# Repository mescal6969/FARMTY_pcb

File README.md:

Farmty – IoT Smart Farming System

Farmty is an IoT-based smart farming system designed to monitor and control farm parameters in real time.  
This repository contains the KiCad PCB design , schematics , and related files for the Farmty hardware.

##  Features
- ESP32-WROOM-32 microcontroller (with WiFi + Bluetooth)
- RS485 sensor support:
  - Soil moisture
  - pH sensor
  - EC (Electrical Conductivity)
  - Temperature
- BME280 (humidity, pressure, temperature sensor)
- Load cell integration (for smart weighing)
- OLED (SSD1306) display
- Stepper motor driver
- Relay control for automation
- PC817 optocoupler isolation
- USB-to-UART via CH340C
- Modular power supply and terminal blocks

---

##  Software
- **Firmware:** ESP-IDF / Arduino framework
- **Programming language:** Python (for data processing) + C++ (for microcontroller)
- **IoT Dashboard:** Cloud-ready, customizable with MQTT/HTTP

---

##  Hardware
- Designed in KiCad
- Includes hierarchical schematics for modularity
- PCB fabrication-ready

##  How to Use
1. Clone this repo:
   ```bash
   https://github.com/mescal6969/FARMTY_pcb
2. Open the project in KiCad.
3. Modify schematics/PCB as needed.
4. Generate Gerber files for manufacturing.
5.Flash ESP32 with firmware to connect to IoT dashboard.

## IoT Integration

Farmty uses the **ESP32 WiFi module** to connect to the cloud.  
It can be integrated with:  
- **Blynk**  
- **ThingsBoard**  
- **Node-RED**  
- **MQTT brokers** (Mosquitto, HiveMQ)  

## License

This project is open-source under the **MIT License**.  
Feel free to use, modify, and share with attribution.

 Author
Allan Ng’ang’a Gacheru
BSc Mechatronics Engineering
Dedan Kimathi University of Technology

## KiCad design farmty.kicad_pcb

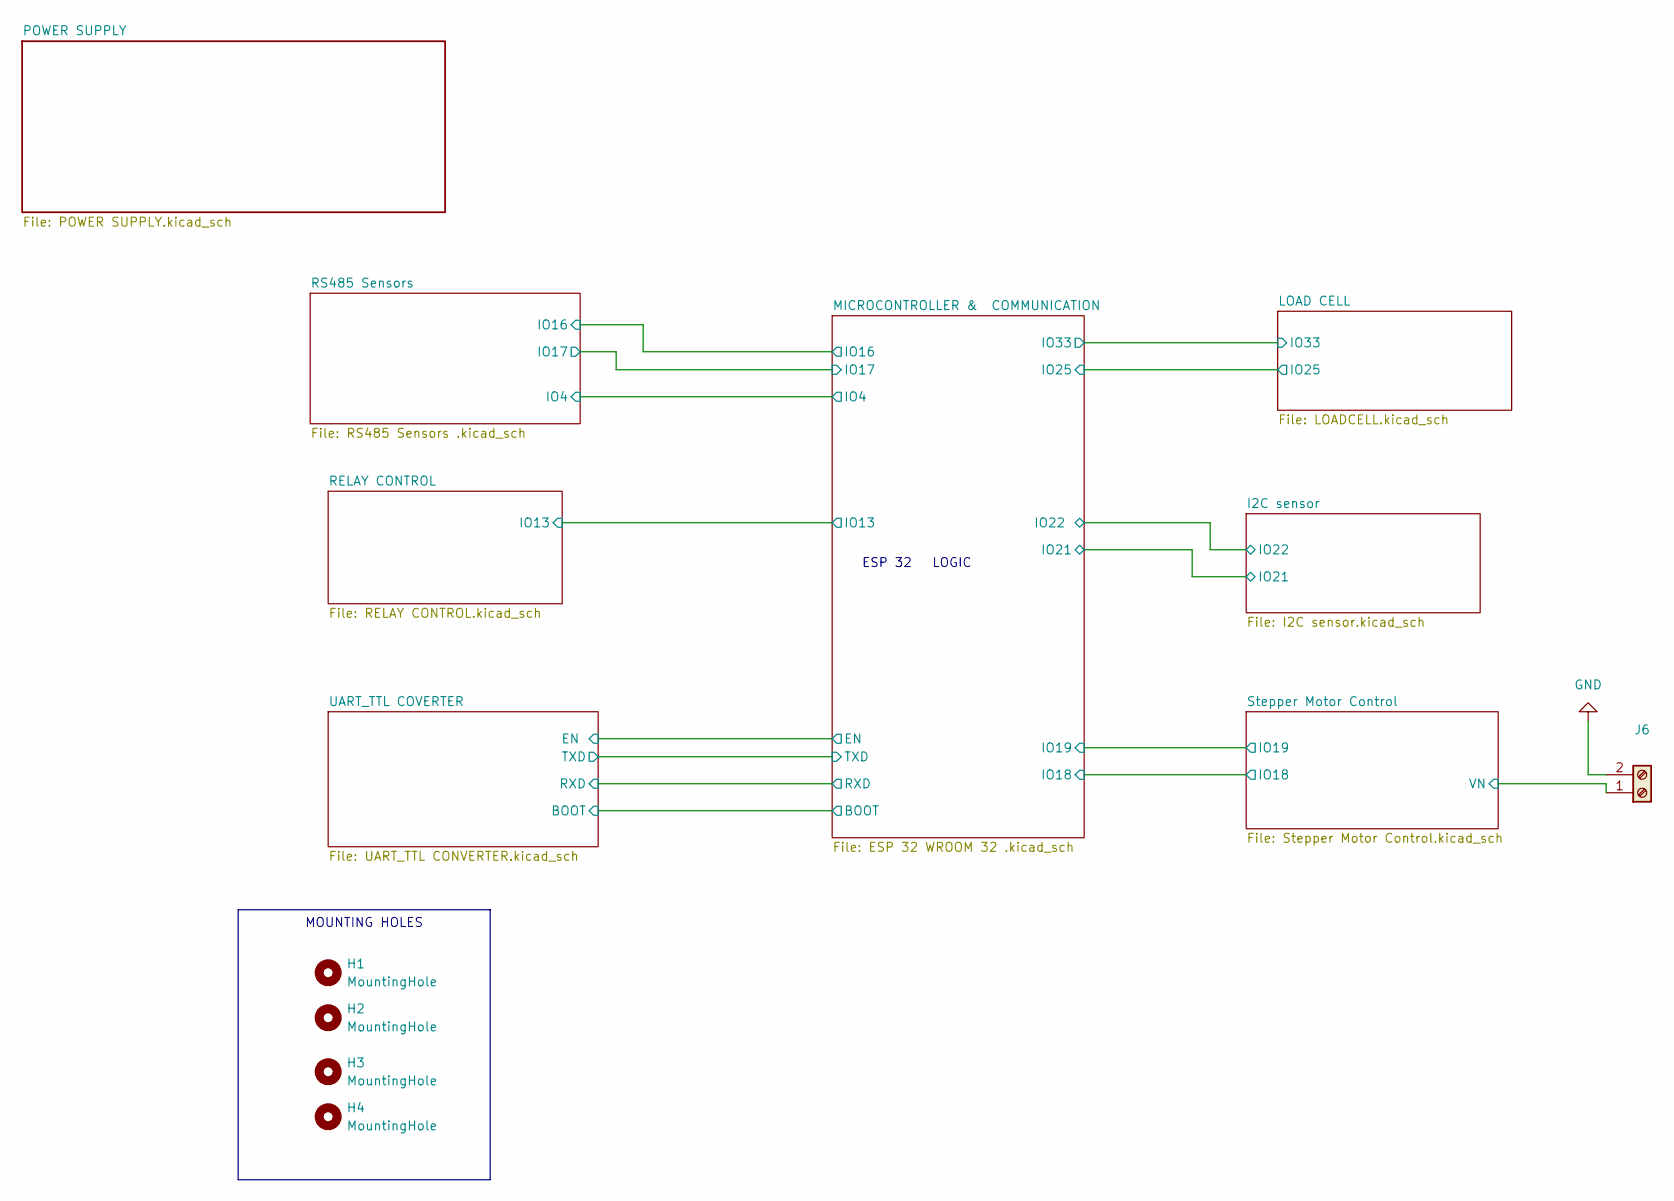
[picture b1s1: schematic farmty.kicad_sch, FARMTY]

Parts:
H1, H2, H3, H4: MountingHole; MountingHole_3.2mm_M3
J6: TerminalBlock_4Ucon_1x02_P3.50mm_Vertical

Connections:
/Stepper Motor Control/VN: J6.1; also elsewhere on the board
GND: J6.2; also elsewhere on the board

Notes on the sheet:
MOUNTING HOLES
ESP 32 LOGIC

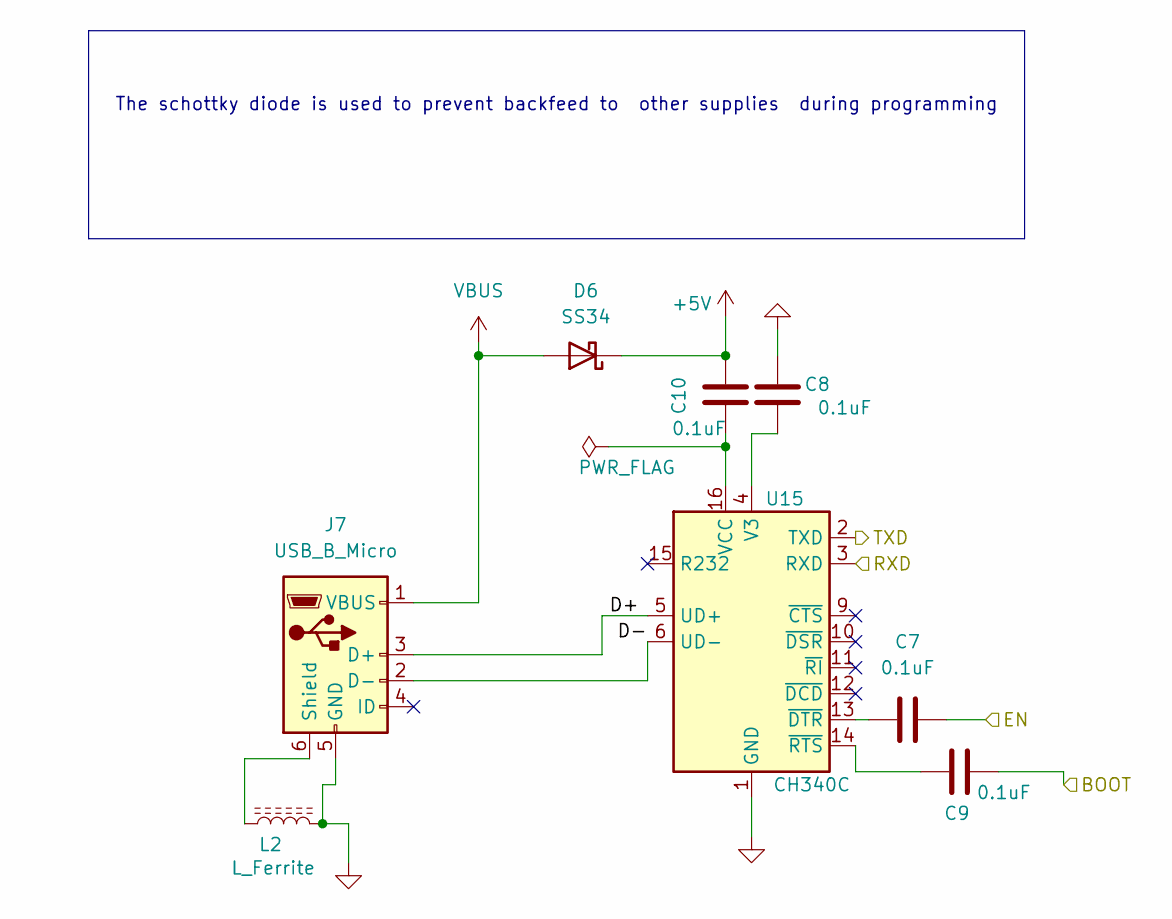
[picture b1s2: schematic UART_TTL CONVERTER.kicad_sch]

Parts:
C7, C8, C9, C10: 0.1uF; C_1808_4520Metric
D6: SS34; D_SMA
J7: USB_B_Micro; USB_Micro-B_Molex-105017-0001
L2: L_Ferrite; L_1806_4516Metric
U15: CH340C; SOIC-16_3.9x9.9mm_P1.27mm

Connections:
+5V: C10.1, D6.1 (K); also elsewhere on the board
/MICROCONTROLLER & COMMUNICATION/BOOT: C9.2; also elsewhere on the board
/MICROCONTROLLER & COMMUNICATION/EN: C7.2; also elsewhere on the board
/MICROCONTROLLER & COMMUNICATION/RXD: U15.3 (RXD); also elsewhere on the board
/MICROCONTROLLER & COMMUNICATION/TXD: U15.2 (TXD); also elsewhere on the board
GND: C8.1, J7.5 (GND), L2.2, U15.1 (GND); also elsewhere on the board
unnamed: J7.3 (D+), U15.5 (UD+)
unnamed: J7.2 (D-), U15.6 (UD-)
unnamed: J7.6 (Shield), L2.1
unnamed: C8.2, U15.4 (V3)
unnamed: C10.2, U15.16 (VCC)
unnamed: C7.1, U15.13 (~DTR)
unnamed: C9.1, U15.14 (~RTS)
VBUS: D6.2 (A), J7.1 (VBUS)

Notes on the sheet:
The schottky diode is used to prevent backfeed to other supplies during programming

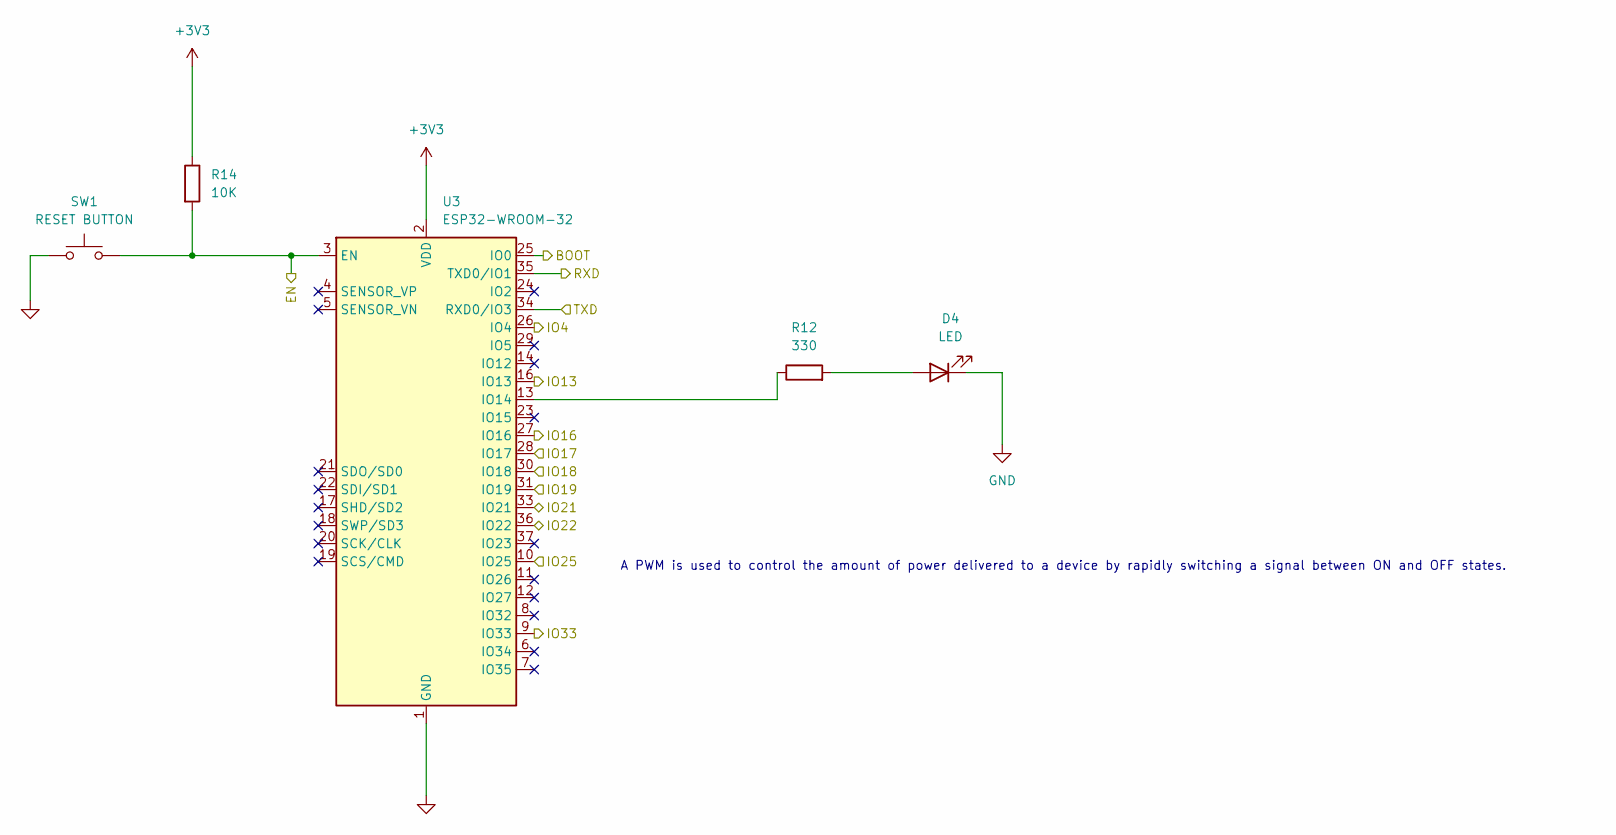
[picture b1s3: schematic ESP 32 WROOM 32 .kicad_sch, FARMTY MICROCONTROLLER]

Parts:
D4: LED; LED_2010_5025Metric
R12: 330; R_0603_1608Metric
R14: 10K; R_0603_1608Metric
SW1: RESET BUTTON; SW_DIP_SPSTx01_Slide_9.78x4.72mm_W7.62mm_P2.54mm
U3: ESP32-WROOM-32

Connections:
+3V3: R14.1, U3.2 (VDD); also elsewhere on the board
/I2C sensor/IO21: U3.33 (IO21); also elsewhere on the board
/I2C sensor/IO22: U3.36 (IO22); also elsewhere on the board
/LOAD CELL/IO25: U3.10 (IO25); also elsewhere on the board
/LOAD CELL/IO33: U3.9 (IO33); also elsewhere on the board
/MICROCONTROLLER & COMMUNICATION/BOOT: U3.25 (IO0); also elsewhere on the board
/MICROCONTROLLER & COMMUNICATION/EN: R14.2, SW1.2, U3.3 (EN); also elsewhere on the board
/MICROCONTROLLER & COMMUNICATION/IO4: U3.26 (IO4); also elsewhere on the board
/MICROCONTROLLER & COMMUNICATION/IO13: U3.16 (IO13); also elsewhere on the board
/MICROCONTROLLER & COMMUNICATION/IO16: U3.27 (IO16); also elsewhere on the board
/MICROCONTROLLER & COMMUNICATION/IO17: U3.28 (IO17); also elsewhere on the board
/MICROCONTROLLER & COMMUNICATION/IO18: U3.30 (IO18); also elsewhere on the board
/MICROCONTROLLER & COMMUNICATION/IO19: U3.31 (IO19); also elsewhere on the board
/MICROCONTROLLER & COMMUNICATION/RXD: U3.35 (TXD0/IO1); also elsewhere on the board
/MICROCONTROLLER & COMMUNICATION/TXD: U3.34 (RXD0/IO3); also elsewhere on the board
GND: D4.1 (K), SW1.1, U3.1 (GND), U3.15 (GND), U3.38 (GND), U3.39 (GND); also elsewhere on the board
unnamed: D4.2 (A), R12.2
unnamed: R12.1, U3.13 (IO14)

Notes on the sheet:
A PWM is used to control the amount of power delivered to a device by rapidly switching a signal between ON and OFF states.

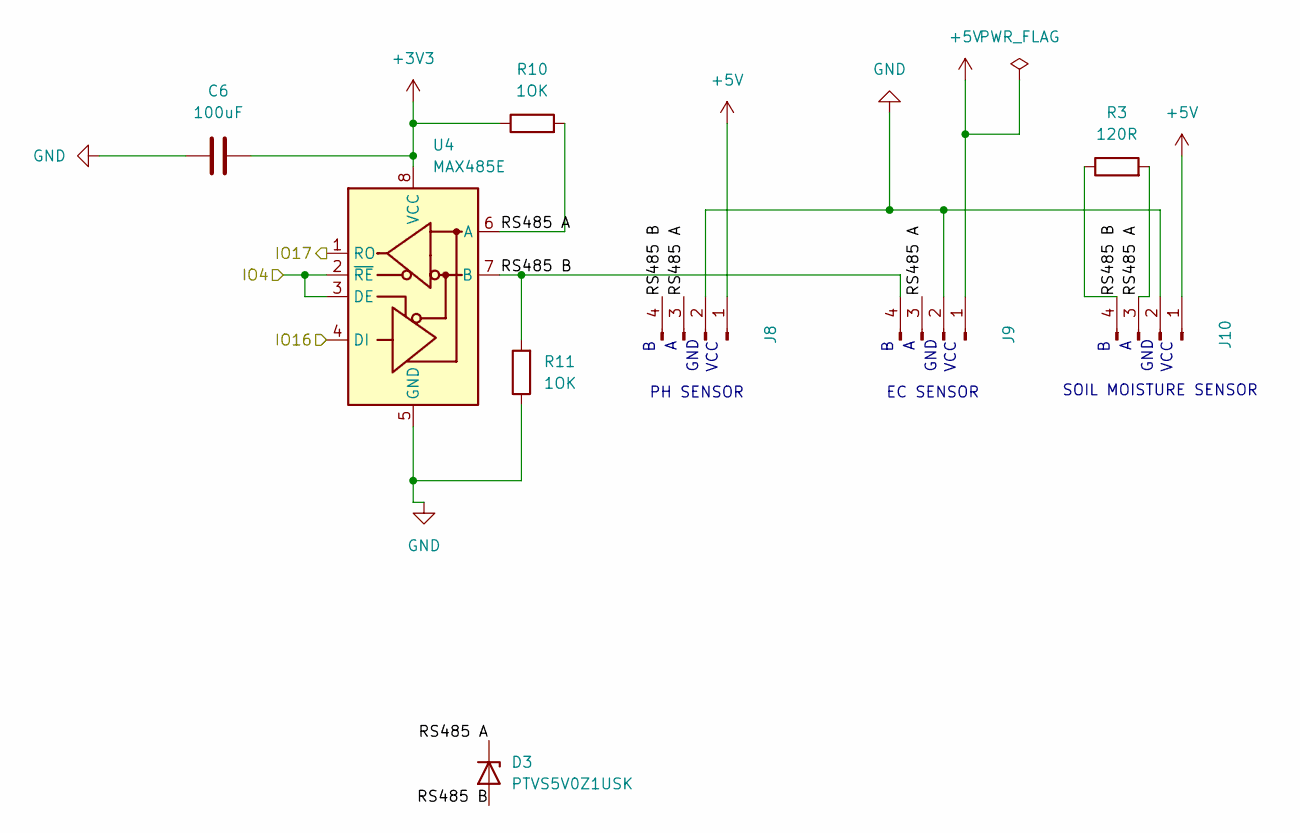
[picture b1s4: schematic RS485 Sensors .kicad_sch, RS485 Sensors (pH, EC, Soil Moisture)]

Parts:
C6: 100uF; C_2220_5750Metric
D3: PTVS5V0Z1USK; Nexperia_DSN1608-2_1.6x0.8mm
J8, J9, J10: Conn_01x04_Pin; PinHeader_1x04_P2.54mm_Vertical
R3: 120R; R_0603_1608Metric
R10, R11: 1OK; R_0603_1608Metric
U4: MAX485E; SOIC-8_3.9x4.9mm_P1.27mm

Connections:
+3V3: C6.2, R10.1, U4.8 (VCC); also elsewhere on the board
+5V: J8.1, J9.1, J10.1; also elsewhere on the board
/MICROCONTROLLER & COMMUNICATION/IO4: U4.2 (~RE), U4.3 (DE); also elsewhere on the board
/MICROCONTROLLER & COMMUNICATION/IO16: U4.4 (DI); also elsewhere on the board
/MICROCONTROLLER & COMMUNICATION/IO17: U4.1 (RO); also elsewhere on the board
/RS485 Sensors/RS485 A: D3.1 (K), J8.3, J9.3, J10.3, R3.2, R10.2, U4.6 (A)
/RS485 Sensors/RS485 B: D3.2 (A), J8.4, J9.4, J10.4, R3.1, R11.2, U4.7 (B)
GND: C6.1, J8.2, J9.2, J10.2, R11.1, U4.5 (GND); also elsewhere on the board

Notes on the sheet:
VCC
EC SENSOR
GND
PH SENSOR
SOIL MOISTURE SENSOR

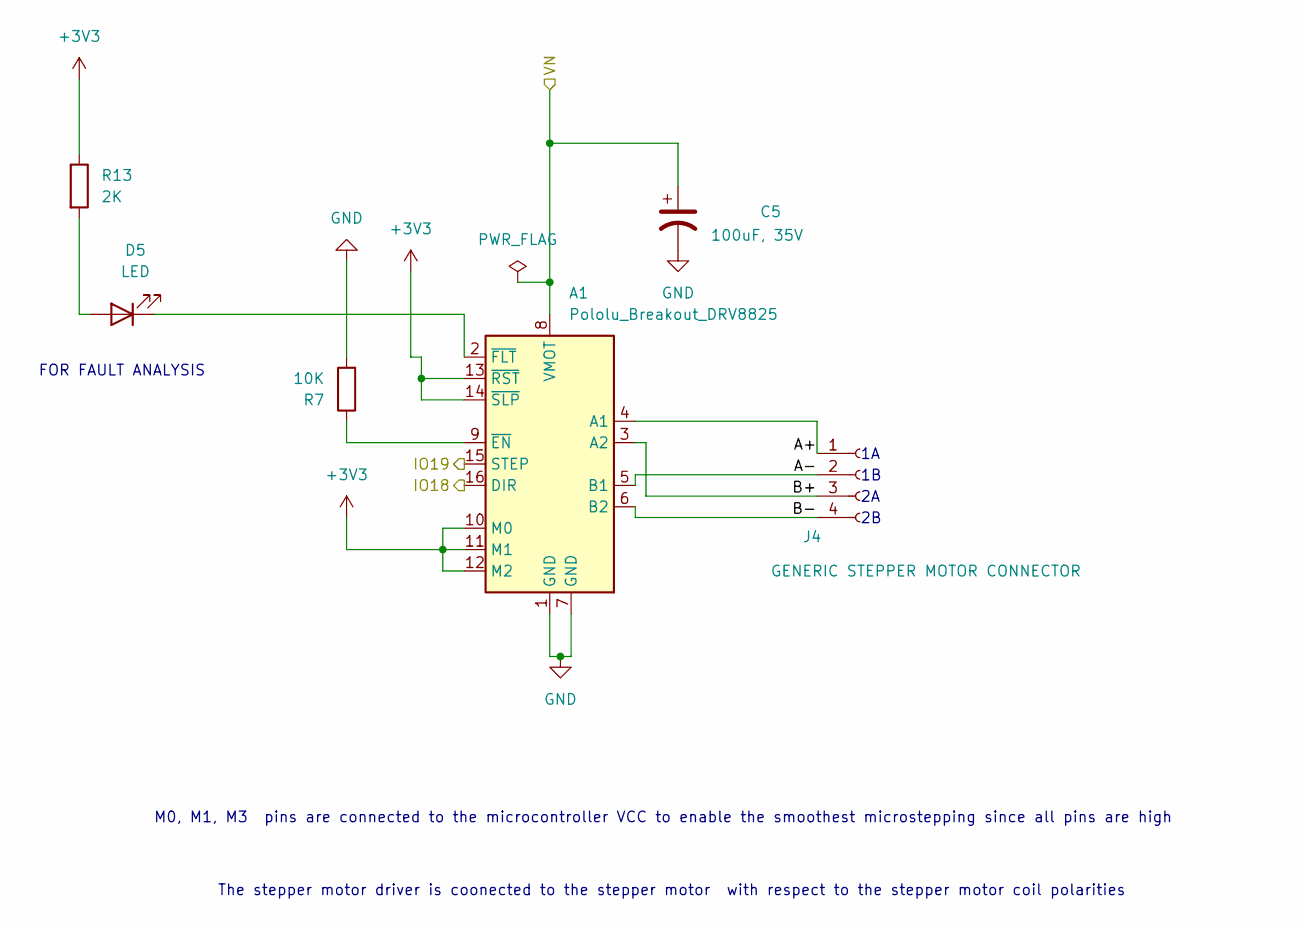
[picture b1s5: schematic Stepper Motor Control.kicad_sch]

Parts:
A1: Pololu_Breakout_DRV8825; Pololu_Breakout-16_15.2x20.3mm
C5: 100uF, 35V; C_2220_5750Metric
D5: LED; LED_D3.0mm
J4: GENERIC STEPPER MOTOR CONNECTOR; PinHeader_1x04_P2.54mm_Vertical
R7: 10K; R_0603_1608Metric
R13: 2K; R_0603_1608Metric

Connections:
+3V3: A1.10 (M0), A1.11 (M1), A1.12 (M2), A1.13 (~RST), A1.14 (~SLP), R13.1; also elsewhere on the board
/MICROCONTROLLER & COMMUNICATION/IO18: A1.16 (DIR); also elsewhere on the board
/MICROCONTROLLER & COMMUNICATION/IO19: A1.15 (STEP); also elsewhere on the board
/Stepper Motor Control/A+: A1.4 (A1), J4.1
/Stepper Motor Control/A-: A1.5 (B1), J4.2
/Stepper Motor Control/B+: A1.3 (A2), J4.3
/Stepper Motor Control/B-: A1.6 (B2), J4.4
/Stepper Motor Control/VN: A1.8 (VMOT), C5.1; also elsewhere on the board
GND: A1.1 (GND), A1.7 (GND), C5.2, R7.2; also elsewhere on the board
unnamed: A1.9 (~EN), R7.1
unnamed: A1.2 (~FLT), D5.1 (K)
unnamed: D5.2 (A), R13.2

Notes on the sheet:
M0, M1, M3 pins are connected to the microcontroller VCC to enable the smoothest microstepping since all pins are high
The stepper motor driver is coonected to the stepper motor with respect to the stepper motor coil polarities
FOR FAULT ANALYSIS

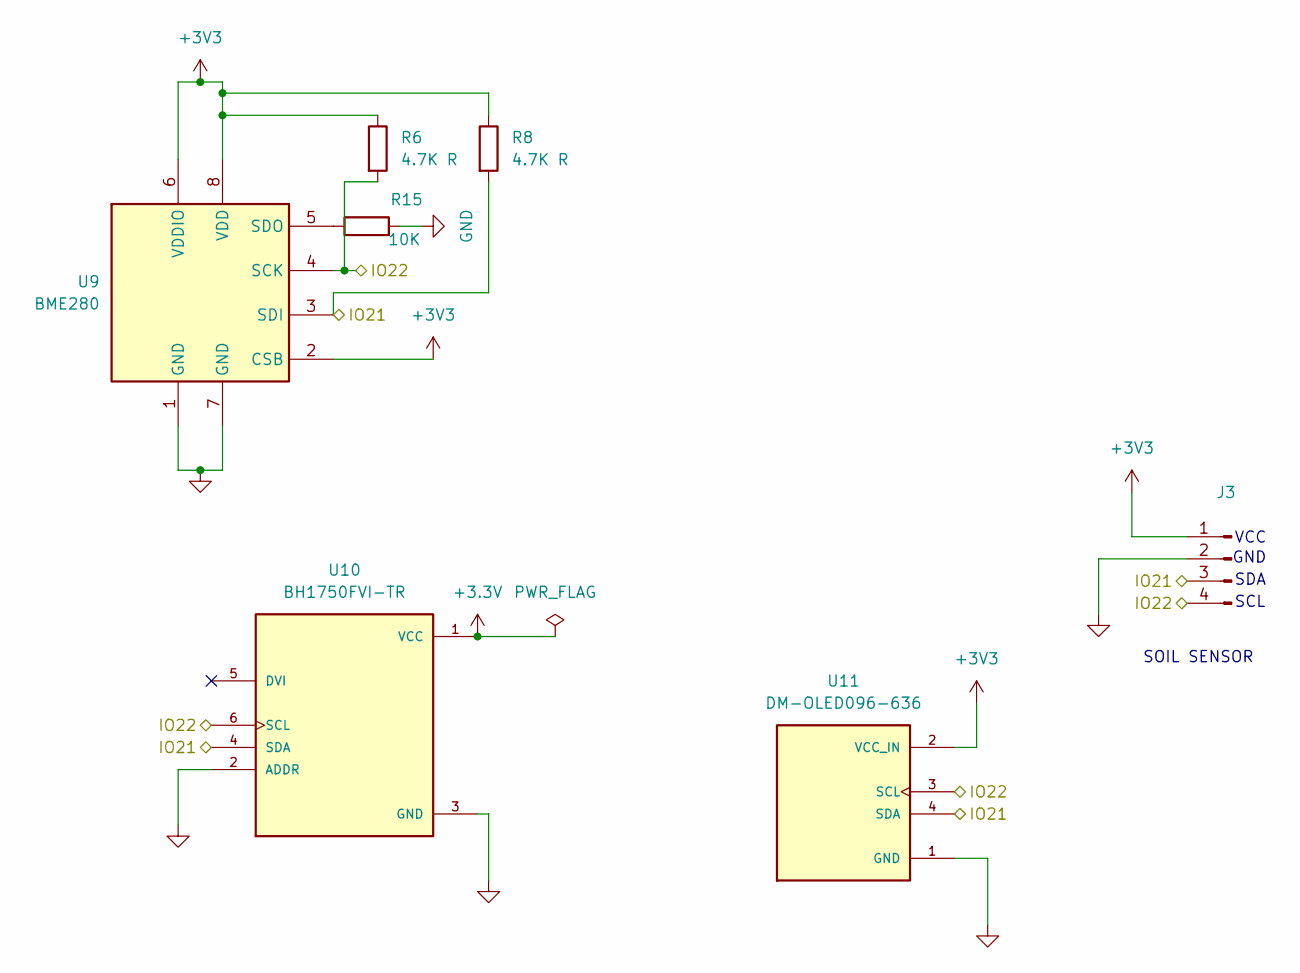
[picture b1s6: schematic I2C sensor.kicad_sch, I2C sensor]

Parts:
J3: Conn_01x04_Pin; PinHeader_1x04_P2.54mm_Vertical
R6, R8: 4.7K R; R_0603_1608Metric
R15: 10K; R_0603_1608Metric
U9: BME280; Bosch_LGA-8_2.5x2.5mm_P0.65mm_ClockwisePinNumbering
U10: BH1750FVI-TR; XDCR_BH1750FVI-TR; PARTREV D
U11: DM-OLED096-636; MODULE_DM-OLED096-636; PARTREV 2018-09-10

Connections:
+3.3V: U10.1 (VCC)
+3V3: J3.1, R6.1, R8.1, U9.2 (CSB), U9.6 (VDDIO), U9.8 (VDD), U11.2 (VCC_IN); also elsewhere on the board
/I2C sensor/IO21: J3.3, R8.2, U9.3 (SDI), U10.4 (SDA), U11.4 (SDA); also elsewhere on the board
/I2C sensor/IO22: J3.4, R6.2, U9.4 (SCK), U10.6 (SCL), U11.3 (SCL); also elsewhere on the board
GND: J3.2, R15.2, U9.1 (GND), U9.7 (GND), U10.2 (ADDR), U10.3 (GND), U11.1 (GND); also elsewhere on the board
unnamed: R15.1, U9.5 (SDO)

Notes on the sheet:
VCC
SCL
SOIL SENSOR
SDA
GND

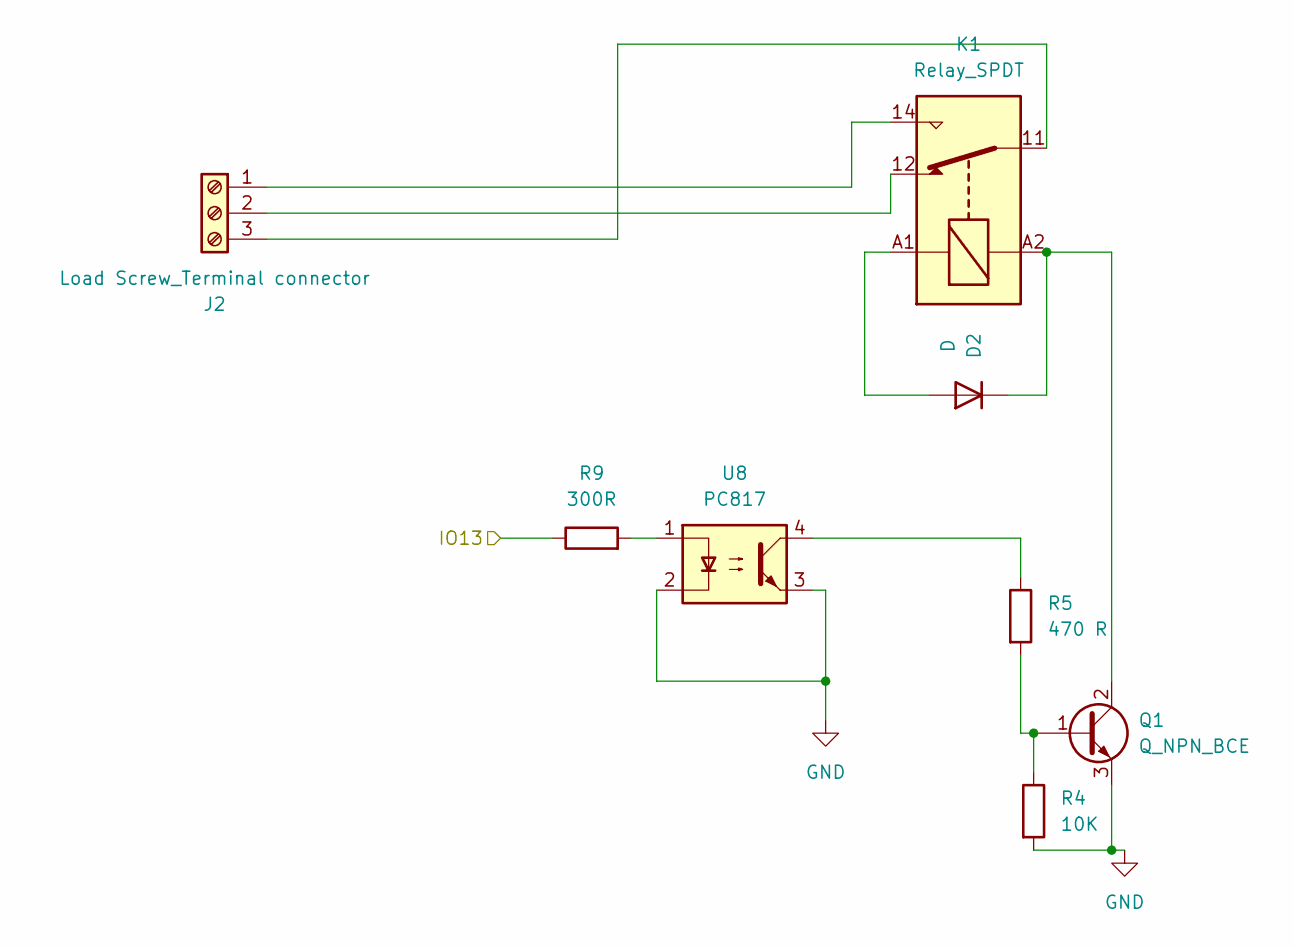
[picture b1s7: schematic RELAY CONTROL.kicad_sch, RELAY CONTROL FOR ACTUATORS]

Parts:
D2: D; D_0805_2012Metric
J2: Load Screw_Terminal connector; Altech_AK100_1x03_P5.00mm
K1: Relay_SPDT; Relay_SPDT_Hongfa_JQC-3FF_0XX-1Z
Q1: Q_NPN_BCE; TO-92_Inline
R4: 10K; R_0603_1608Metric
R5: 470 R; R_0603_1608Metric
R9: 300R; R_0603_1608Metric
U8: PC817; DIP-4_W7.62mm

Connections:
/MICROCONTROLLER & COMMUNICATION/IO13: R9.1; also elsewhere on the board
GND: Q1.3 (E), R4.2, U8.2, U8.3; also elsewhere on the board
unnamed: D2.2 (A), K1.A1
unnamed: D2.1 (K), K1.A2, Q1.2 (C)
unnamed: J2.1, K1.14
unnamed: J2.2, K1.12
unnamed: J2.3, K1.11
unnamed: Q1.1 (B), R4.1, R5.2
unnamed: R5.1, U8.4
unnamed: R9.2, U8.1

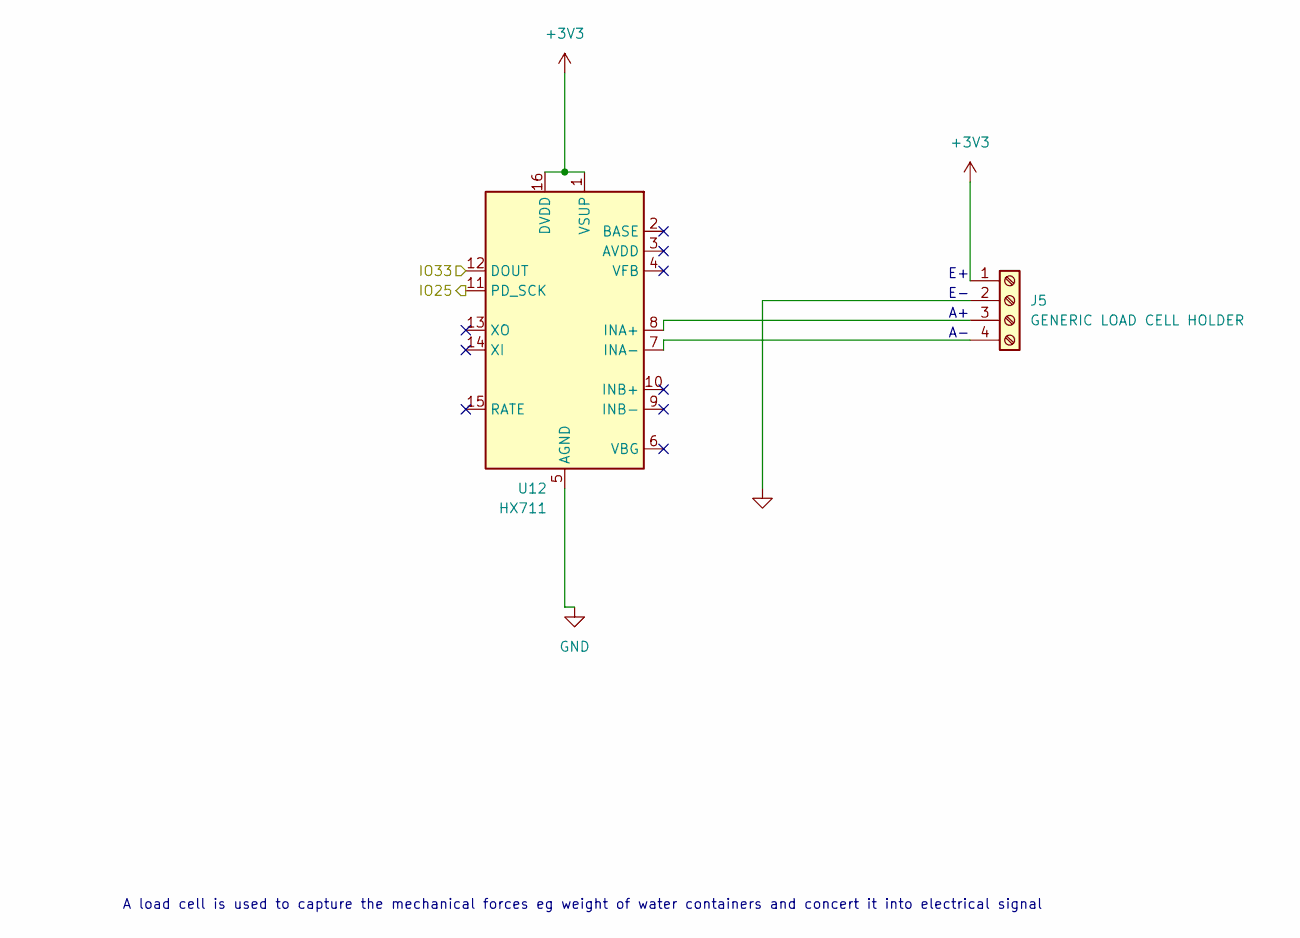
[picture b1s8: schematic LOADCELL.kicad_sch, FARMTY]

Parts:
J5: GENERIC LOAD CELL HOLDER; Altech_AK100_1x04_P5.00mm
U12: HX711; SOP-16_3.9x9.9mm_P1.27mm

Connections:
+3V3: J5.1, U12.1 (VSUP), U12.16 (DVDD); also elsewhere on the board
/LOAD CELL/IO25: U12.11 (PD_SCK); also elsewhere on the board
/LOAD CELL/IO33: U12.12 (DOUT); also elsewhere on the board
GND: J5.2, U12.5 (AGND); also elsewhere on the board
unnamed: J5.3, U12.8 (INA+)
unnamed: J5.4, U12.7 (INA-)

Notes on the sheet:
A load cell is used to capture the mechanical forces eg weight of water containers and concert it into electrical signal

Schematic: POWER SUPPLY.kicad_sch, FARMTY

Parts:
C1: 1000uF, 16V; C_2220_5750Metric
C2: 220uF, 10V; C_2220_5750Metric
C3: 100uF, 6.3V; C_1808_4520Metric
C4: 220uF, 25V; C_2220_5750Metric
D1: SS34; D_SMA
F1: 2.5A; Fuse_1206_3216Metric
J11: EJ508B; MPD_EJ508B; PARTREV G
L1: 33uH, 3A; L_1806_4516Metric
R1: 3.3k; R_0603_1608Metric
R2: 1k; R_0603_1608Metric
U1: LM2596S-5; TO-263-5_TabPin3
U2: AMS1117-3.3; SOT-223-3_TabPin2

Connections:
5V: C1.1, L1.2
+3V3: C3.1, U2.2 (VO); also elsewhere on the board
+12V: F1.1, J11.1
/POWER SUPPLY/+12Vin: D1.2 (A), F1.2
GND: C1.2, C2.2, C3.2, C4.2, J11.2, R2.2, U1.3 (GND), U2.1 (GND); also elsewhere on the board
unnamed: C4.1, D1.1 (K), U1.1 (VIN)
unnamed: R1.2, R2.1, U1.4 (FB)
unnamed: L1.1, R1.1, U1.2 (OUT)
unnamed: C2.1, U2.3 (VI)

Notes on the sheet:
POWER_SUPPLY

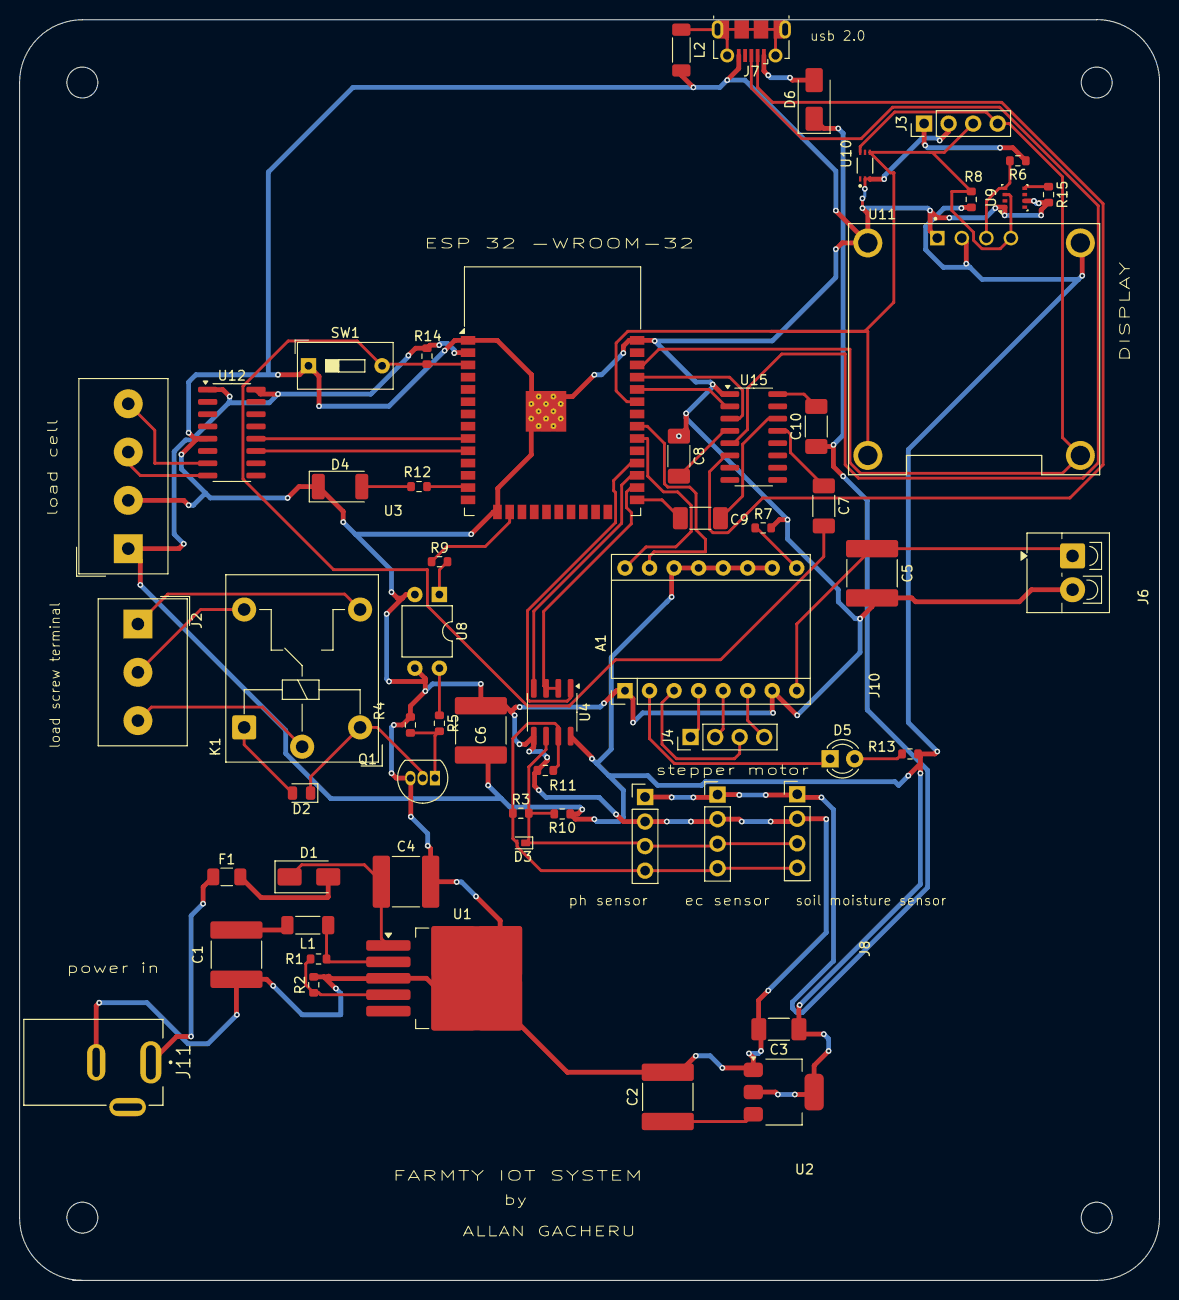
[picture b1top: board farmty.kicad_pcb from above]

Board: 2 copper layers, 118.0 x 130.5 mm, 62 parts (0 on the bottom side), 55 nets.

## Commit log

2025-09-24 README.md
